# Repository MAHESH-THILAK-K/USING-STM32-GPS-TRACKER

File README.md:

# 📌 Project Overview

STM32-GPS-TRACKER is a compact, reliable, and industry-oriented GPS tracking system built around an **STM32 microcontroller** and the **SIM808 GSM/GPS module**. The system enables **real-time location tracking** and **cellular data transmission** for IoT and telemetry applications such as vehicle tracking, asset monitoring, and remote sensing.

The schematic and PCB are designed with **strong power integrity, EMI control, and manufacturability**, targeting a **4-layer PCB** suitable for real-world deployment.

---

## 🧩 System Architecture

| Block                    | Description                                           |
| ------------------------ | ----------------------------------------------------- |
| Power Input & Protection | Accepts 12 V input with fuse and surge protection     |
| DC-DC Regulation         | High-efficiency buck converter generates stable 3.3 V |
| Main Controller          | STM32 microcontroller manages system logic            |
| Communication Module     | SIM808 provides GSM + GPS functionality               |
| SIM Interface            | SIM card socket with ESD protection                   |
| RF Section               | U.FL connectors for GSM and GPS antennas              |
| User Interface           | Push buttons and status LEDs                          |
| Debug & Expansion        | SWD and header pins for programming and I/O           |

---

## 🔧 Core Controller – STM32 MCU

| Feature           | Description                  |
| ----------------- | ---------------------------- |
| MCU               | STM32 (ARM Cortex-M0 series) |
| Operating Voltage | 3.3 V                        |
| Clock Source      | External crystal oscillator  |
| Programming       | SWD (SWDIO, SWCLK, NRST)     |
| Communication     | UART interface to SIM808     |
| Control Signals   | SIM808 PWRKEY, RESET         |
| Indicators        | Status LEDs via GPIO         |

The STM32 acts as the **central controller**, handling GSM commands, GPS data processing, and system coordination.

---

## 📡 GSM/GPS Communication – SIM808

| Feature   | Description                          |
| --------- | ------------------------------------ |
| Module    | SIM808 GSM + GPS                     |
| GSM       | Cellular data communication          |
| GPS       | Satellite-based positioning          |
| Interface | UART (TX/RX)                         |
| Control   | Dedicated PWRKEY and RESET lines     |
| Antennas  | Separate GSM and GPS U.FL connectors |

The SIM808 enables **accurate positioning** and **wide-area data transmission**, making the system suitable for mobile and remote applications.

---

## 🔋 Power Design

| Feature       | Description                          |
| ------------- | ------------------------------------ |
| Input Voltage | 12 V DC                              |
| Regulator     | TPS5430 buck converter               |
| Output        | 3.3 V regulated rail                 |
| Filtering     | Bulk + ceramic decoupling capacitors |
| Protection    | Fuse and transient suppression       |

The switching regulator is designed to handle **high current bursts** from GSM transmission while maintaining voltage stability.

---

## 🛡️ SIM Card & Protection

| Feature             | Description                    |
| ------------------- | ------------------------------ |
| SIM Socket          | Standard SIM interface         |
| Signal Conditioning | Series resistors               |
| ESD Protection      | Dedicated ESD diode array      |
| Decoupling          | Local capacitor for SIM supply |

This ensures **reliable SIM operation** and protection against electrostatic discharge.

---

## 📶 RF & Antenna Design

| Feature       | Description                       |
| ------------- | --------------------------------- |
| GSM Antenna   | U.FL connector                    |
| GPS Antenna   | U.FL connector                    |
| Grounding     | Proper RF grounding and isolation |
| Layout Intent | Antenna keep-out zones respected  |

Designed to ensure **clean RF performance** and reduced interference.

---

## 🧪 PCB Design (4-Layer Optimized)

| Layer   | Purpose                       |
| ------- | ----------------------------- |
| Top     | Components and signal routing |
| Inner-1 | Solid GND plane               |
| Inner-2 | 3.3 V power plane             |
| Bottom  | Signal routing                |

Benefits:

* Low impedance power delivery
* Reduced EMI
* Stable GSM/GPS performance
* Improved thermal and electrical reliability

## 🚀 Engineering Notes

* Designed for **4-layer PCB manufacturing**
* Robust power integrity for GSM current spikes
* EMI-aware grounding and routing
* Modular and expandable design
* Suitable for academic, hobby, and industry use

---

## 👤 Author

**MAHESH THILAK (MTK)**
Embedded Systems | PCB Design | IoT | Robotics

---

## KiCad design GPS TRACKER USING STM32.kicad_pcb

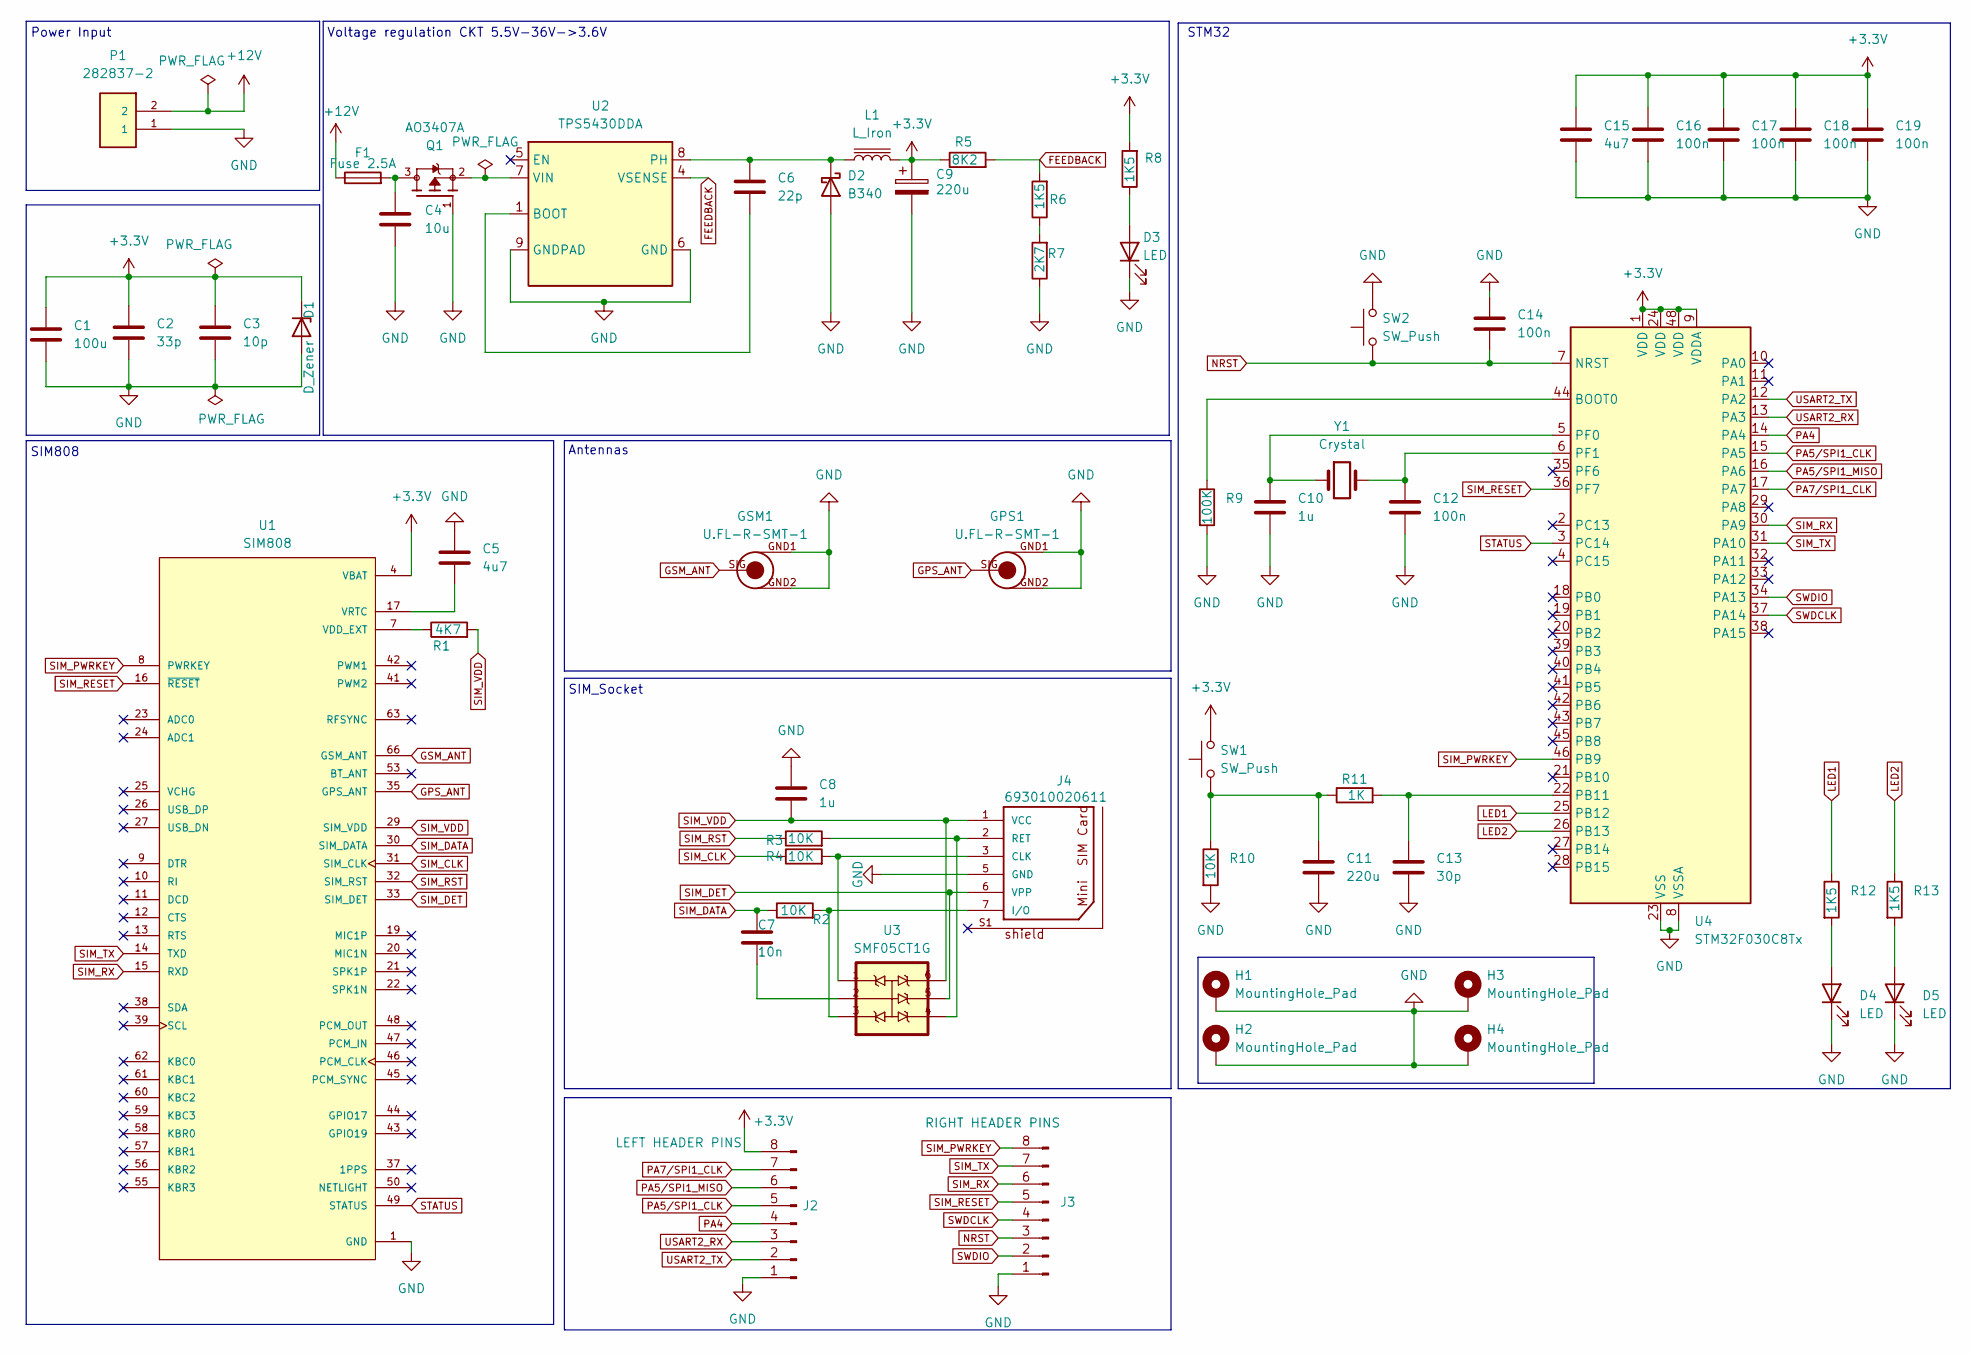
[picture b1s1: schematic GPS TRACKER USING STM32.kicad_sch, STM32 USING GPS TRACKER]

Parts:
C1: 100u; C_0603_1608Metric_Pad1.08x0.95mm_HandSolder
C2: 33p; C_0603_1608Metric_Pad1.08x0.95mm_HandSolder
C3: 10p; C_0603_1608Metric_Pad1.08x0.95mm_HandSolder
C4: 10u; C_0603_1608Metric_Pad1.08x0.95mm_HandSolder
C5, C15: 4u7; C_0603_1608Metric_Pad1.08x0.95mm_HandSolder
C6: 22p; C_0603_1608Metric_Pad1.08x0.95mm_HandSolder
C7: 10n; C_0603_1608Metric_Pad1.08x0.95mm_HandSolder
C8, C10: 1u; C_0603_1608Metric_Pad1.08x0.95mm_HandSolder
C9: 220u; CP_EIA-7343-15_Kemet-W
C11: 220u; C_0603_1608Metric_Pad1.08x0.95mm_HandSolder
C12, C14, C16, C17, C18, C19: 100n; C_0603_1608Metric_Pad1.08x0.95mm_HandSolder
C13: 30p; C_0603_1608Metric_Pad1.08x0.95mm_HandSolder
D1: D_Zener; D_0805_2012Metric
D2: B340; D_SMC
D3, D4, D5: LED; LED_0201_0603Metric
F1: Fuse 2.5A; Fuse_0402_1005Metric
GPS1: U.FL-R-SMT-1
GSM1: U.FL-R-SMT-1
H1, H2, H3, H4: MountingHole_Pad; MountingHole_2.5mm_Pad_Via
J2: LEFT HEADER PINS; PinHeader_1x08_P2.54mm_Vertical
J3: RIGHT HEADER PINS; PinHeader_1x08_P2.54mm_Vertical
J4: 693010020611
L1: L_Iron; L_10.4x10.4_H4.8
P1: 282837-2; TE_282837-2; PARTREV G3
Q1: AO3407A; SOT65P210X110-6N; PARTREV 5
R1: 4K7; R_0201_0603Metric_Pad0.64x0.40mm_HandSolder
R2, R3, R4, R10: 10K; R_0201_0603Metric_Pad0.64x0.40mm_HandSolder
R5: 8K2; R_0201_0603Metric_Pad0.64x0.40mm_HandSolder
R6, R8, R12, R13: 1K5; R_0201_0603Metric_Pad0.64x0.40mm_HandSolder
R7: 2K7; R_0201_0603Metric_Pad0.64x0.40mm_HandSolder
R9: 100K; R_0201_0603Metric_Pad0.64x0.40mm_HandSolder
R11: 1K; R_0201_0603Metric_Pad0.64x0.40mm_HandSolder
SW1, SW2: SW_Push; SW_Push_1P1T_NO_CK_KSC6xxJ
U1: SIM808; XCVR_SIM808; PARTREV 1.03
U2: TPS5430DDA; TI_SO-PowerPAD-8_ThermalVias
U3: SMF05CT1G; SOT65P210X110-6N
U4: STM32F030C8Tx; LQFP-48_7x7mm_P0.5mm
Y1: Crystal; Crystal_SMD_5032-2Pin_5.0x3.2mm

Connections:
+3.3V: C1.1, C2.1, C3.1, C9.1, C15.1, C16.1, C17.1, C18.1, C19.1, D1.1 (K), J2.8, L1.2, R5.1, R8.2, SW1.2, U1.4 (VBAT), U1.5 (VBAT), U1.6 (VBAT), U4.1 (VDD), U4.9 (VDDA), U4.24 (VDD), U4.48 (VDD)
+12V: F1.1, P1.2
FEEDBACK: R5.2, R6.2, U2.4 (VSENSE)
GND: C1.2, C2.2, C3.2, C4.2, C5.1, C8.1, C9.2, C10.2, C11.2, C12.2, C13.2, C14.1, C15.2, C16.2, C17.2, C18.2, C19.2, D1.2 (A), D2.2 (A), D3.1 (K), D4.1 (K), D5.1 (K), GPS1.GND1, GPS1.GND2, GSM1.GND1, GSM1.GND2, H1.1, H2.1, H3.1, H4.1, J2.1, J3.1, J4.5 (GND), P1.1, Q1.1, R7.1, R9.2, R10.2, SW2.2, U1.1 (GND), U1.2 (GND), U1.3 (GND), U1.18 (GND), U1.28 (GND), U1.34 (GND), U1.36 (GND), U1.40 (GND), U1.51 (GND), U1.52 (GND), U1.54 (GND), U1.64 (GND), U1.65 (GND), U1.67 (GND), U1.68 (GND), U2.6 (GND), U2.9 (GNDPAD), U4.8 (VSSA), U4.23 (VSS), U4.47 (VSS)
GPS_ANT: GPS1.SIG, U1.35 (GPS_ANT)
GSM_ANT: GSM1.SIG, U1.66 (GSM_ANT)
LED1: R12.1, U4.25 (PB12)
LED2: R13.1, U4.26 (PB13)
NRST: C14.2, J3.3, SW2.1, U4.7 (NRST)
unnamed: C4.1, F1.2, Q1.3
unnamed: C7.2, U3.2
unnamed: C11.1, R10.1, R11.1, SW1.1
unnamed: C6.1, D2.1 (K), L1.1, U2.8 (PH)
unnamed: D3.2 (A), R8.1
unnamed: D4.2 (A), R12.2
unnamed: D5.2 (A), R13.2
unnamed: J4.3 (CLK), R4.2, U3.1
unnamed: J4.7 (I/O), R2.2, U3.3
unnamed: J4.2 (RET), R3.2, U3.4
unnamed: R6.1, R7.2
unnamed: R1.1, U1.7 (VDD_EXT)
unnamed: C5.2, U1.17 (VRTC)
unnamed: C6.2, U2.1 (BOOT)
unnamed: Q1.2, U2.7 (VIN)
unnamed: R9.1, U4.44 (BOOT0)
unnamed: C13.1, R11.2, U4.22 (PB11)
unnamed: C10.1, U4.5 (PF0), Y1.1
unnamed: C12.1, U4.6 (PF1), Y1.2
PA4: J2.4, U4.14 (PA4)
PA5/SPI1_CLK: J2.5, U4.15 (PA5)
PA5/SPI1_MISO: J2.6, U4.16 (PA6)
PA7/SPI1_CLK: J2.7, U4.17 (PA7)
SIM_CLK: R4.1, U1.31 (SIM_CLK)
SIM_DATA: C7.1, R2.1, U1.30 (SIM_DATA)
SIM_DET: J4.6 (VPP), U1.33 (SIM_DET), U3.5
SIM_PWRKEY: J3.8, U1.8 (PWRKEY), U4.46 (PB9)
SIM_RESET: J3.5, U1.16 (~RESET), U4.36 (PF7)
SIM_RST: R3.1, U1.32 (SIM_RST)
SIM_RX: J3.6, U1.15 (RXD), U4.30 (PA9)
SIM_TX: J3.7, U1.14 (TXD), U4.31 (PA10)
SIM_VDD: C8.2, J4.1 (VCC), R1.2, U1.29 (SIM_VDD), U3.6
STATUS: U1.49 (STATUS), U4.3 (PC14)
SWDCLK: J3.4, U4.37 (PA14)
SWDIO: J3.2, U4.34 (PA13)
USART2_RX: J2.3, U4.13 (PA3)
USART2_TX: J2.2, U4.12 (PA2)

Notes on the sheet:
SIM_Socket
SIM808
Power Input
STM32
Voltage regulation CKT 5.5V-36V->3.6V
Antennas

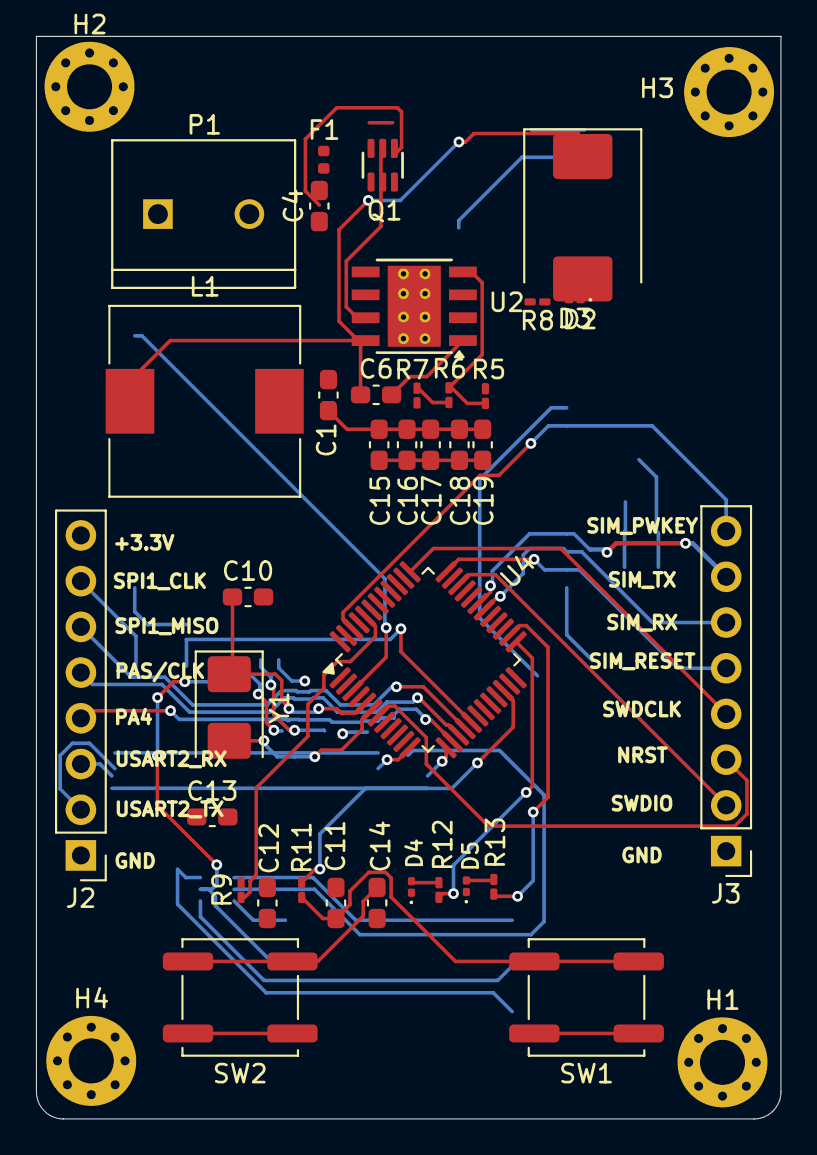
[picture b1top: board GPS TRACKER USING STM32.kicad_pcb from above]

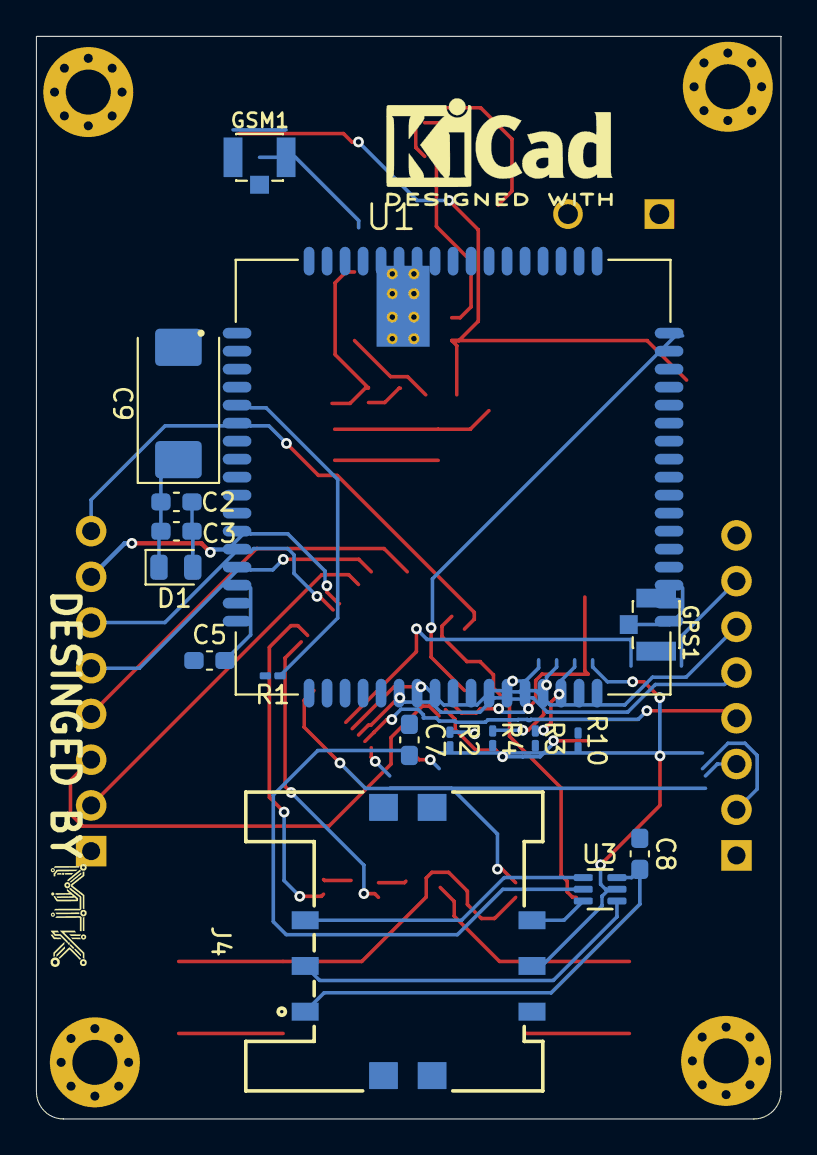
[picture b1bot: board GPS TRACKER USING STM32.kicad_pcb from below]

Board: 4 copper layers, 41.4 x 60.1 mm, 57 parts (17 on the bottom side), 46 nets.

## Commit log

2026-04-24 Create Gerber
2026-04-24 Create Gerber
